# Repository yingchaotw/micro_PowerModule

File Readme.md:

# µPower Module

1. Purpose：

 - DC/DC Programmable small-wattage power supply
 - This project is [Open Source Hardware](https://www.oshwa.org/definition/chinese/)

2. Scope：
 - RFQ
     1. [x] Over voltage protection circuit
     2. [x] Support [MikroBus](https://www.mikroe.com/mikrobus) Foot Position
     3. [x] Positive and negative load voltage signals can be controlled by the H-bridge
     4. [x] Display voltage/current/wattage [Nokia 5110 LCD](https://github.com/EleonoreMizo/pedalevite/blob/master/doc/datasheets/Philips%20PCD8544%20-%20IC%2C%2048x84%20pixels%20matrix%20LCD%20controller%20(Nokia%205110).pdf), [TI-Nokia 5110 LCD](https://www.ti.com/lit/ml/swrp182/swrp182.pdf), [Nokia5110 LCD ](https://components101.com/displays/nokia-5110-lcd)
     5. [ ] MCU auto-regulator function
     6. [ ] Real time display of voltage and current
     7. [ ] Use a led to display local or remote mode
        1. [x] Standard Commands for Programmable Instruments

# HW Block Diagram

<BR/>
plug-in module. ex. Temperature sensor, etc.. <br/>

[Schematic Readme](./Circuit_microPowerModule/Readme.md)

# SW FlowChart
```mermaid
flowchart TD
subgraph "System Initialization"
  a("Check Communication<BR>(UART/I2C/SPI/..)") --> b(Check ADC) --> c(Read Sensor) --> d[buzzer <br> Make a sound]
end

subgraph "main"
    A(Start) --> B[System<br>Initialization]
    B --> C[Select Mode]
    C -->D["Remote <PC>"]
    C -->E["Local <encoder>"]
end

```

# Candidate Components

The required hardware units are divided into the following 6 items.
1. Power
2. Microcontroller
3. Interface
4. Sensor (Current/temperature)
5. Connector
6. Debug port

# PIN Assessment

[Raspberry Pi RP2040 GPIO Function](https://datasheets.raspberrypi.com/rp2040/rp2040-datasheet.pdf#_gpio_functions)

```
GPIO00 UART0 (Tx) --> RS485 (In)
GPIO01 UART0 (Rx) <-- RS485 (Out)
GPIO02 I2C1 (SDA) <-> (*Option) MikroBus SDA
GPIO03 I2C1 (SCL) --> (*Option) MikroBus SCL
GPIO04 I2C0 (SDA) <-> Power Management
GPIO05 I2C0 (SCL) --> Power Management
GPIO06 DS (MOSI)  --> Display Serial Input
GPIO07 DS (CLK)   --> Display Clock Input
GPIO08 UART1 (Tx) --> (*Option) MikroBus Tx
GPIO09 UART1 (Rx) <-- (*Option) MikroBus Rx
GPIO10 SPI1 (SCK) --> (*Option) MikroBus SCK
GPIO11 SPI1 (Tx)  --> (*Option) MikroBus SDI
GPIO12 SPI1 (Rx)  <-- (*Option) MikroBus SDO
GPIO13 SPI1 (nCS) --> (*Option) MikroBus CSS
GPIO14 DS (CE)    --> Display Chip Enable
GPIO15 DS (DC)    --> Display Data Command
GPIO16 PWM0_A     --> Buzzer
GPIO17 MkBus_RST  --> (*Option) MikroBus Reset
GPIO18 PWM1_A     --> (*Option) MikroBus PWM
GPIO19 PIO1_IRQ1  --> (*Option) MikroBus INT
GPIO20 PWM2_A     --> Encoder A phase
GPIO21 PWM2_B     --> Encoder B phase
GPIO22 RS_485 W/R --> RS485 (W/R)
GPIO23 DS_RST     --> Display Reset
GPIO24 ENC_SW     <-- Encoder Push Switch
GPIO25 PWM4 B     --> WS2512 LED Control
GPIO26 Monitor    <-- Input Power Monitor
GPIO27 ADC1       <-- (*Option) MikroBus ADC
GPIO28 Output_CTRL<-- Buck / Boost Switch
GPIO29 *Polarity  --> H-Bridge Control Load (Forward/Reverse)
```

# Potocol

[About Spec](./Document/Specification/Spec_link.md)
[Standard Commands for Programmable Instruments](https://www.ivifoundation.org/docs/scpi-99.pdf)

# Licenses & Disclaimer

 <br/> This work is licensed under a <a rel="license" href="https://www.gnu.org/licenses/quick-guide-gplv3.en.html"> GNU General Public License v3</a>.

If you have other ideas or suggestions, please feel free to submit an issue.
Welcome fork this repositories to provide contributions, or [buy me a coffee](https://ko-fi.com/yingchao_tw). thanks :)

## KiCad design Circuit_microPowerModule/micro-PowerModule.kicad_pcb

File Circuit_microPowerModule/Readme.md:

# Schematic

# ERC Report

```
ERC report (Thu 15 Jun 2023 20:53:31 CST, Encoding UTF8)

***** Sheet /

***** Sheet /main_contorl/

***** Sheet /Input_power/

***** Sheet /OutputPower/

***** Sheet /peripheral/

** ERC messages: 0  Errors 0  Warnings 0
```
[ERC File](./ERC.rpt)

# Incldue Library
[MikroBus](https://github.com/tclarke/kicad-mikroBUS)

# License & Disclaimer

 <br/> This work is licensed under a <a rel="license" href="https://www.gnu.org/licenses/quick-guide-gplv3.en.html"> GNU General Public License v3</a>.

If you have other ideas or suggestions, please feel free to submit an issue.
Welcome fork this repositories to provide contributions, or [buy me a coffee](https://ko-fi.com/yingchao_tw). thanks :)

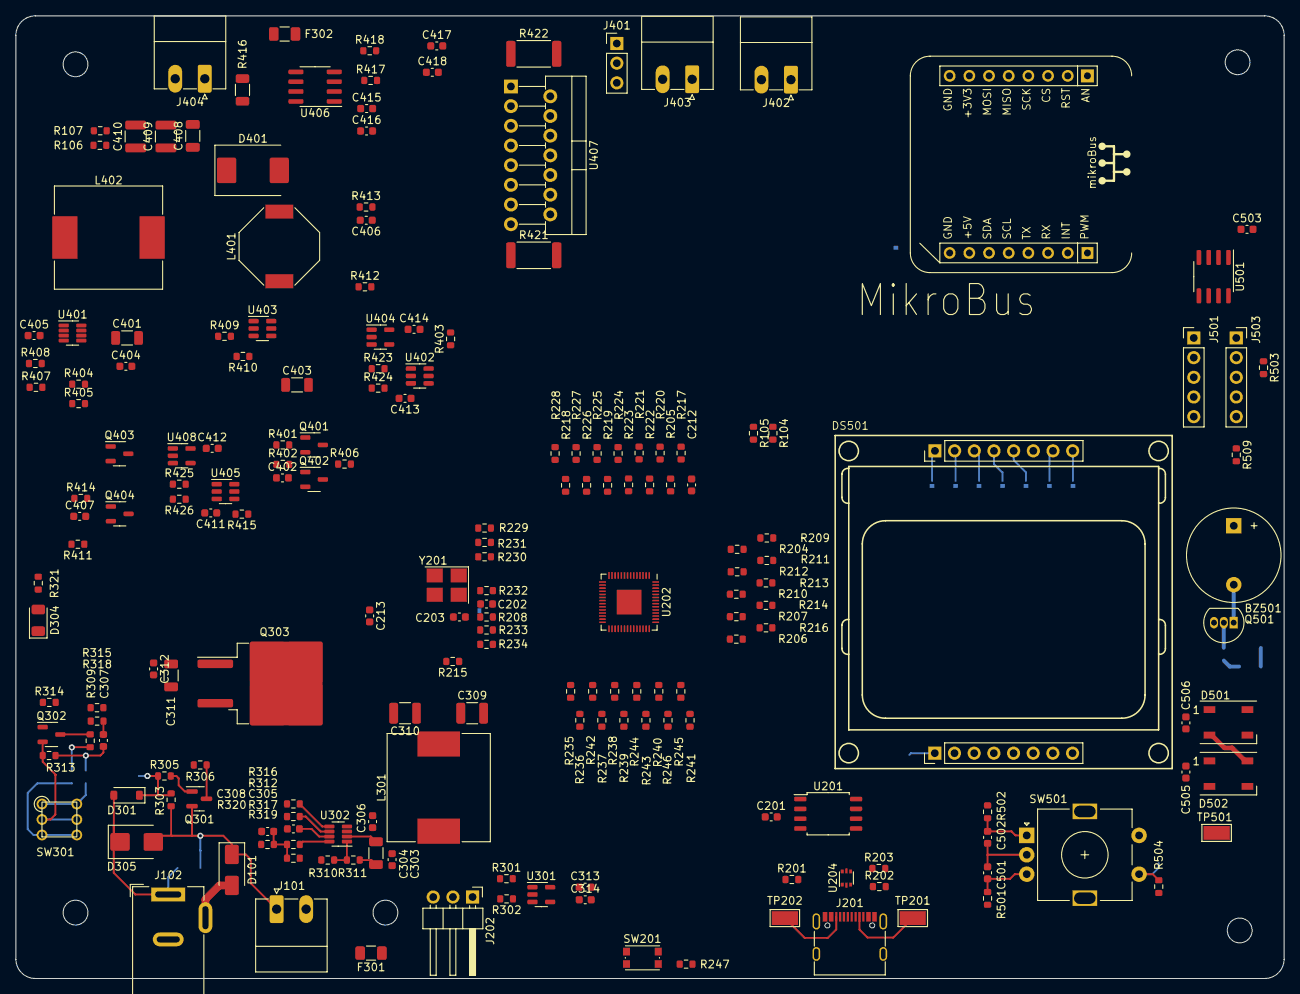
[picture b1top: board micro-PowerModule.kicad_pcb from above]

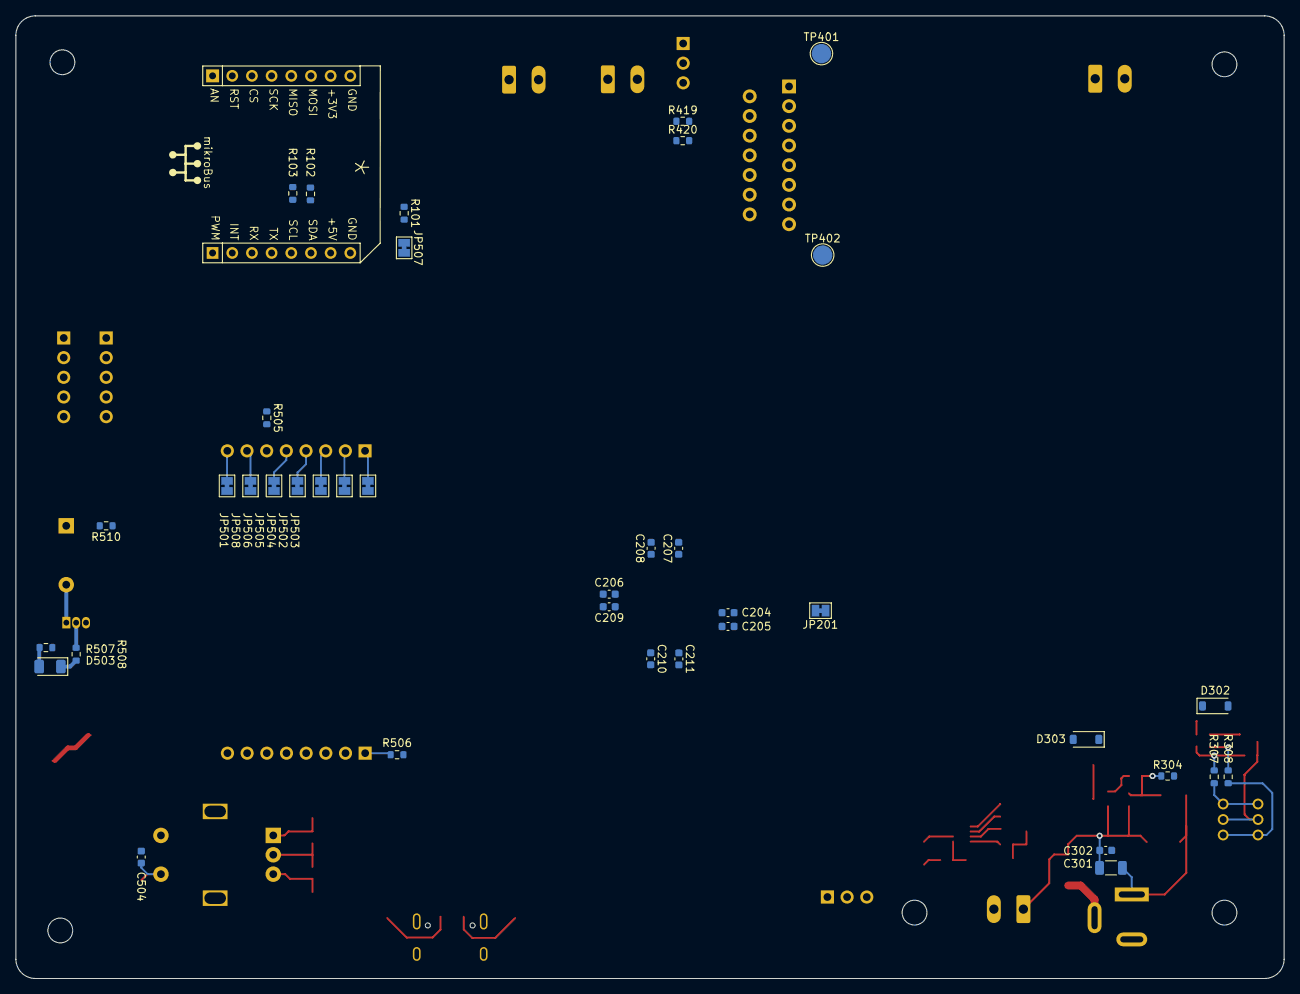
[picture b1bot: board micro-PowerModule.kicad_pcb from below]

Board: 2 copper layers, 163.7 x 124.2 mm, 235 parts (38 on the bottom side), 177 nets.

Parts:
BZ501: Buzzer; Buzzer_12x9.5RM7.6
C201, C204, C205, C206, C207, C208, C209, C210, C211, C212, C303, C305, C306, C313, C314, C404, C405, C411, C412, C413, C414, C415, C416, C417, C418, C501, C502, C503, C505, C506: 100nF/50V; C_0603_1608Metric
C202, C203: 15pF/50V; C_0603_1608Metric
C213, C402, C407: 10pF/50V; C_0603_1608Metric
C301, C311: 47u/50V; C_1206_3216Metric
C302, C312: 100n/50V; C_0603_1608Metric
C304, C401, C403, C408: 22uF/50V; C_1206_3216Metric
C307: 10n/50V; C_0603_1608Metric
C308, C406: 33pF/50V; C_0603_1608Metric
C309, C310, C409, C410: 22uF/50V; C_1210_3225Metric
C504: 10nF/50V; C_0603_1608Metric
D101: SS54; D_SMA
D301: Zener_24V/500mW; D_SOD-123
D302: DNP; D_SOD-123
D303: Zener_20V/500mW; D_SOD-123
D304: LED_Green; LED_1206_3216Metric
D305: TPSMB36CA; D_SMB
D401: SS34; D_SMC
D501, D502: WS2812B; LED_WS2812B_PLCC4_5.0x5.0mm_P3.2mm
D503: LED_Blue; LED_1206_3216Metric
DS501: NOKIA 5110; Nokia_5110_module
F301, F302: 60V/100mA; Fuse_1206_3216Metric
J101, J402, J403, J404: Screw_Terminal_01x02; PhoenixContact_MC_1,5_2-G-3.81_1x02_P3.81mm_Horizontal
J102: Jack-DC; BarrelJack_Wuerth_6941xx301002
J201: USB_C_Receptacle_USB2.0; USB_C_Receptacle_G-Switch_GT-USB-7010ASV
J202: Debug; PinHeader_1x03_P2.54mm_Horizontal
J401: Conn_01x03; PinHeader_1x03_P2.54mm_Vertical
J501: HDR-2.54 Male 1x5; PinHeader_1x05_P2.54mm_Vertical
J502: MikroBus; MIKROBUS_CONN
J503: HDR-2.54 Female 1x5; PinSocket_1x05_P2.54mm_Vertical
JP201, JP501, JP502, JP503, JP504, JP505, JP506, JP507, JP508: SolderJumper_2_Bridged; SolderJumper-2_P1.3mm_Bridged_Pad1.0x1.5mm
L301, L402: 4.7uH; L_Sunlord_MWSA1204S-4R7
L401: 33uH; L_Bourns-SRU1028_10.0x10.0mm
Q301: MMBT3906; SOT-23
Q302, Q402, Q404: RK7002BM; SOT-23-3
Q303: IRF5305S; TO-263-2
Q401, Q403: RU1C002ZP; SOT-23-3
Q501: S8550; TO-92_Inline
R101, R201, R216, R309, R318, R401, R411, R417, R418, R423, R425, R506, R509, R510: 0R/5%; R_0603_1608Metric
R102, R103, R106, R107, R204, R205, R303, R304, R305, R306, R307, R501, R502, R504: 10K/5%; R_0603_1608Metric
R104, R105: 22R/5%; R_0603_1608Metric
R202, R203: 5.1K/5%; R_0603_1608Metric
R206, R207: 27R/5%; R_0603_1608Metric
R208, R314, R321, R403, R415, R419, R420, R424, R426, R507, R508: 1K/5%; R_0603_1608Metric
R209, R210, R211, R212, R213, R214, R217, R218, R219, R220, R221, R222, R223, R224, R225, R226, R227, R228, R229, R230, R231, R232, R233, R234, R235, R236, R237, R238, R239, R240, R241, R242, R243, R244, R245, R246, R316, R407: 10R/5%; R_0603_1608Metric
R215, R247: 1K/DNP; R_0603_1608Metric
R301, R402, R414: 22K/5%; R_0603_1608Metric
R302: 3.3K/5%; R_0603_1608Metric
R308: 100R/5%; R_0603_1608Metric
R310, R313, R315, R404, R408: 100K/5%; R_0603_1608Metric
R311: 7.5K/5%; R_0603_1608Metric
R312: 499K/5%; R_0603_1608Metric
R317: 33K/5%; R_0603_1608Metric
R319: 12.7K/5%; R_0603_1608Metric
R320: 40.2K/5%; R_0603_1608Metric
R405: 9K1/5%; R_0603_1608Metric
R406: 47R/5%; R_0603_1608Metric
R409, R410: 2.2K/5%; R_0603_1608Metric
R412: 62K/5%; R_0603_1608Metric
R413: 20.5K/5%; R_0603_1608Metric
R416: 0.1R/1%; R_1206_3216Metric
R421, R422: 0.5R/5%; R_2512_6332Metric
R503: 120R/5%; R_0603_1608Metric
R505: DNP; R_0603_1608Metric
REF1, REF1#2, REF1#3, REF1#4, REF1#5: MountingHole_3.2mm_M3_ISO7380
SW201: KMR2; SW_Push_1P1T_NO_CK_KMR2
SW301: SW_DPDT_x2; SW_DIP_5176_SPDT
SW501: RotaryEncoder_Switch; RotaryEncoder_Alps_EC11E-Switch_Vertical_H20mm
TP201, TP202, TP501: TestPoint_Small; TestPoint_Keystone_5015_Micro-Minature
TP401, TP402: TestPoint; TestPoint_Pad_D2.5mm
U201: W25Q128JVS; SOIC-8_5.23x5.23mm_P1.27mm
U202: RP2040; QFN-56-1EP_7x7mm_P0.4mm_EP3.2x3.2mm
U204: USBLC6-2P6; SOT-666
U301, U404, U408: OPA376xxDBV; SOT-23-5
U302, U401: MP2315S; TSOT-23-8
U402, U405: MCP4725xxx-xCH; SOT-23-6
U403: MT3608; SOT-23-6
U406: INA219BxD; SOIC-8_3.9x4.9mm_P1.27mm
U407: L298N; TO-220-15_P2.54x2.54mm_StaggerOdd_Lead4.58mm_Vertical
U501: MAX485E; SOIC-8_3.9x4.9mm_P1.27mm
Y201: 12MHz; Crystal_SMD_SeikoEpson_FA238V-4Pin_3.2x2.5mm_HandSoldering

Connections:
+1V2: C204.1, C205.1, C206.1, R216.1, U202.23 (DVDD), U202.50 (DVDD)
+3V3: C201.1, C207.1, C208.1, C209.1, C210.1, C211.1, C212.1, C308.2, C309.1, C310.1, C313.1, C314.1, C411.1, C412.1, C413.1, C414.1, C415.1, C416.1, C503.1, C505.1, C506.1, D501.1 (VDD), D502.1 (VDD), J502.7, JP508.2 (B), L301.2, Q401.1 (D), Q403.1 (D), R102.1, R103.1, R106.1, R107.1, R204.2, R205.2, R247.1, R320.1, R402.2, R414.2, R415.2, R419.1, R501.1, R502.1, R504.1, R506.1, R507.1, R510.1, U201.8 (VCC), U202.1 (IOVDD), U202.10 (IOVDD), U202.22 (IOVDD), U202.33 (IOVDD), U202.42 (IOVDD), U202.43 (ADC_AVDD), U202.44 (VREG_IN), U202.48 (USB_VDD), U202.49 (IOVDD), U301.5 (V+), U402.3 (VDD), U404.5 (V+), U405.3 (VDD), U406.5 (VS), U408.5 (V+), U501.8 (VCC)
+5V: C417.1, C418.1, J502.10, R509.2, U407.4 (Vs)
+VDC: C303.1, C304.1, C311.1, C312.1, C401.1, C403.1, L401.1, Q303.1 (D), R312.2, R321.1, U302.2 (IN), U401.2 (IN), U403.5 (IN)
/BUCK/~BOOST: R104.2, R245.2
/Buzzer_PWM: D503.1 (K), R233.2, R508.1
/Forward/~Reverse: R105.2, R246.2
/Mk_ADC: J502.1, R244.2
/Mk_CS: J502.3, R230.2
/Mk_INT: J502.15, R236.2
/Mk_PWM: J502.16, R235.2
/Mk_RST: J502.2, R234.2
/Mk_Rx: J502.14, R226.2
/Mk_SCL: J502.12, R103.2, R220.2
/Mk_SDA: J502.11, R102.2, R219.2
/Mk_SDI: J502.6, R228.2
/Mk_SDK: J502.4, R227.2
/Mk_SDO: J502.5, R229.2
/Mk_Tx: J502.13, R225.2
/OutputPower/Boost_FB: R410.2, U408.1, U408.4 (-)
/OutputPower/BuckBoostOutput: C408.1, C409.1, C410.1, D401.1 (K), L402.2, R409.1, R416.1, U406.8 (IN+)
/OutputPower/Buck_EN/Boost_~EN: R104.1, R401.1
/OutputPower/Buck_FB: R412.2, U404.1, U404.4 (-)
/OutputPower/EN_MP2315S: C402.1, Q401.2 (G), Q402.2 (G), R401.2, R402.1, U401.6 (EN)
/OutputPower/EN_MT3608: R406.2, U403.4 (EN)
/OutputPower/H_Bridge_Out1: J402.1, U407.2 (OUT1)
/OutputPower/H_Bridge_Out2: J402.2, U407.3 (OUT2)
/OutputPower/H_Bridge_Out3: J403.1, U407.13 (OUT3)
/OutputPower/H_Bridge_Out4: J403.2, U407.14 (OUT4)
/OutputPower/Load_Forward: C407.1, Q403.2 (G), Q404.2 (G), R411.2, R414.1, U407.5 (IN1), U407.10 (IN3)
/OutputPower/Load_Reverse: Q403.3 (S), Q404.1 (D), U407.7 (IN2), U407.12 (IN4)
/OutputPower/Load_direction: R105.1, R411.1
/OutputPower/PWR_OUT: C406.2, J404.1, R413.1, R416.2, U406.7 (IN-), U407.9 (Vss)
/PM_SCL: R106.2, R221.2, U402.5 (SCL), U405.5 (SCL), U406.4 (SCL)
/PM_SDA: R107.2, R222.2, U402.4 (SDA), U405.4 (SDA), U406.3 (SDA)
/PWR_IN: C301.1, C302.1, C307.1, D101.1 (K), D303.1 (K), D305.2 (A2), J101.1, Q301.2 (E), Q303.3 (S), R301.1, R303.1, R307.1, R313.1, R315.1
/PWR_Monitor: R243.2, U301.1, U301.4 (-)
/RP_DS_CHIPENABLE: JP502.1 (A), R231.2
/RP_DS_CLK: JP506.1 (A), R224.2
/RP_DS_DATACMD: JP504.1 (A), R232.2
/RP_DS_MOSI: JP505.1 (A), R223.2
/RP_DS_RESET: JP503.1 (A), R240.2
/RP_ENC_A: C502.1, R237.2, R502.2, SW501.A
/RP_ENC_B: C501.1, R238.2, R501.2, SW501.B
/RP_ENC_SW: C504.1, R241.2, R504.2, SW501.S1
/UARTrx_RS485in: R217.2, U501.4 (DI)
/UARTtx_RS485out: R218.2, U501.1 (RO)
/main_contorl/LET_CTRL: D501.4 (DIN), R242.2
/main_contorl/QSPI_NSS: R204.1, R209.2, U201.1 (~CS)
/main_contorl/QSPI_SCLK: R214.2, U201.6 (CLK)
/main_contorl/QSPI_SD0: R210.2, U201.5 (DI(IO0))
/main_contorl/QSPI_SD1: R211.2, U201.2 (DO(IO1))
/main_contorl/QSPI_SD2: R212.2, U201.3 (IO2)
/main_contorl/QSPI_SD3: R213.2, U201.7 (IO3)
/main_contorl/RS485_W/~R: R239.2, U501.2 (~RE), U501.3 (DE)
/main_contorl/SWCLK: J202.1, U202.24 (SWCLK)
/main_contorl/SWDIO: J202.3, U202.25 (SWD)
/main_contorl/USB+: R206.2, U204.4 (I/O2)
/main_contorl/USB-: R207.2, U204.6 (I/O1)
/main_contorl/USB_N: J201.A7 (D-), J201.B7 (D-), U204.1 (I/O1)
/main_contorl/USB_P: J201.A6 (D+), J201.B6 (D+), U204.3 (I/O2)
/main_contorl/~RESET: C213.1, R205.1, R247.2, SW201.2, U202.26 (RUN)
/main_contorl/~USB_N: R207.1, U202.46 (USB_DM)
/main_contorl/~USB_P: R206.1, U202.47 (USB_DP)
/peripheral/485A: J501.3, J503.3, R503.2, U501.6 (A)
/peripheral/485B: J501.2, J503.2, R503.1, U501.7 (B)
/peripheral/DS_Backlight: DS501.7b (BL), DS501.8a (BL), JP508.1 (A)
/peripheral/DS_ChipEnable: DS501.2b (CE), DS501.3a (SEC), JP502.2 (B)
/peripheral/DS_Clock: DS501.5b (CLK), DS501.7a (SCLK), JP506.2 (B)
/peripheral/DS_Data/Command: DS501.3b (DC), DS501.5a (D/C), JP504.2 (B)
/peripheral/DS_Serial_Data: DS501.4b (DIN), DS501.6a (DN/MOSI), JP505.2 (B)
/peripheral/DS_~Reset: DS501.1b (RST), DS501.4a (RST), JP503.2 (B)
/peripheral/M_GND: J502.8, J502.9, JP507.2 (B)
/peripheral/Mikro_GND: JP507.1 (A), R101.2
GNDPWR: C301.2, C302.2, C303.2, C304.2, C305.2, C309.2, C310.2, C311.2, C312.2, C401.2, C403.2, C404.2, C408.2, C409.2, C410.2, D301.2 (A), D304.1 (K), D305.1 (A1), F301.2, F302.1, J101.2, J102.1, J102.2, J404.2, R304.2, R306.2, R308.2, R309.2, R311.1, R319.2, R405.1, R421.2, R422.2, U302.4 (GND), U401.4 (GND), U403.2 (GND), U407.8 (GND)
GNDREF: C201.2, C204.2, C205.2, C206.2, C207.2, C208.2, C209.2, C210.2, C211.2, C212.2, C213.2, C313.2, C314.2, C402.2, C407.2, C411.2, C412.2, C413.2, C414.2, C415.2, C416.2, C417.2, C418.2, C501.2, C502.2, C503.2, C504.2, C505.2, C506.2, D501.3 (VSS), D502.3 (VSS), DS501.2a (GND), DS501.8b (GND), F301.1, F302.2, J201.A1 (GND), J201.A12 (GND), J201.B1 (GND), J201.B12 (GND), J202.2, JP201.1 (A), JP501.1 (A), Q402.3 (S), Q404.3 (S), Q501.3 (C), R101.1, R201.2, R202.2, R203.1, R302.2, R403.2, R417.2, R418.2, R420.2, R424.1, R426.1, SW201.1, SW501.C, SW501.S2, U201.4 (GND), U202.57 (GND), U204.2 (GND), U301.2 (V-), U402.2 (VSS), U404.2 (V-), U405.2 (VSS), U406.6 (GND), U408.2 (V-), U501.5 (GND), Y201.2, Y201.4
unnamed: BZ501.2 (+), Q501.1 (E)
unnamed: BZ501.1 (-), R510.2
unnamed: C202.1, Y201.1
unnamed: C203.1, Y201.3
unnamed: C203.2, R208.2
unnamed: C306.1, R316.2
unnamed: C308.1, R317.1, R319.1, R320.2
unnamed: C405.1, R407.2
unnamed: C406.1, R408.1, R412.1, R413.2
unnamed: D101.2 (A), J102.3
unnamed: D301.1 (K), R303.2, R304.1, R305.1
unnamed: D302.2 (A), R314.2, R315.2, R318.1
unnamed: C307.2, D302.1 (K), D303.2 (A), Q303.2 (G), R318.2
unnamed: D304.2 (A), R321.2
unnamed: D401.2 (A), L401.2, U403.1 (SW)
unnamed: D501.2 (DOUT), D502.4 (DIN)
unnamed: D502.2 (DOUT), TP501.1
unnamed: D503.2 (A), R507.2
unnamed: DS501.1a (VCC), DS501.6b (VCC), R505.2, R506.2
unnamed: J201.A5 (CC1), R202.1
unnamed: J201.B5 (CC2), R203.2
unnamed: J201.A8 (SBU1), TP201.1
unnamed: J201.B8 (SBU2), TP202.1
unnamed: J201.S1 (SHIELD), R201.1
unnamed: J401.1, R419.2
unnamed: J401.2, U407.6 (EnA), U407.11 (EnB)
unnamed: J401.3, R420.1
unnamed: J501.1, J503.1, JP501.2 (B)
unnamed: JP201.2 (B), U202.19 (TESTEN)
unnamed: Q301.1 (B), R305.2
unnamed: Q301.3 (C), R306.1
unnamed: Q302.1 (D), R314.1
unnamed: Q302.2 (G), R313.2, SW301.2 (B), SW301.5 (B)
unnamed: Q302.3 (S), R309.1
unnamed: Q401.3 (S), Q402.1 (D), R406.1
unnamed: Q501.2 (B), R508.2
unnamed: R307.2, SW301.1 (A), SW301.4 (A)
unnamed: R308.1, SW301.3 (C), SW301.6 (C)
unnamed: R217.1, U202.2 (GPIO0)
unnamed: R218.1, U202.3 (GPIO1)
unnamed: R219.1, U202.4 (GPIO2)
unnamed: R220.1, U202.5 (GPIO3)
unnamed: R221.1, U202.6 (GPIO4)
unnamed: R222.1, U202.7 (GPIO5)
unnamed: R223.1, U202.8 (GPIO6)
unnamed: R224.1, U202.9 (GPIO7)
unnamed: R225.1, U202.11 (GPIO8)
unnamed: R226.1, U202.12 (GPIO9)
unnamed: R227.1, U202.13 (GPIO10)
unnamed: R228.1, U202.14 (GPIO11)
unnamed: R229.1, U202.15 (GPIO12)
unnamed: R230.1, U202.16 (GPIO13)
unnamed: R231.1, U202.17 (GPIO14)
unnamed: R232.1, U202.18 (GPIO15)
unnamed: R233.1, U202.27 (GPIO16)
unnamed: R234.1, U202.28 (GPIO17)
unnamed: R235.1, U202.29 (GPIO18)
unnamed: R236.1, U202.30 (GPIO19)
unnamed: R237.1, U202.31 (GPIO20)
unnamed: R238.1, U202.32 (GPIO21)
unnamed: R239.1, U202.34 (GPIO22)
unnamed: R240.1, U202.35 (GPIO23)
unnamed: R241.1, U202.36 (GPIO24)
unnamed: R242.1, U202.37 (GPIO25)
unnamed: R243.1, U202.38 (GPIO26_ADC0)
unnamed: R244.1, U202.39 (GPIO27_ADC1)
unnamed: R245.1, U202.40 (GPIO28_ADC2)
unnamed: R246.1, U202.41 (GPIO29_ADC3)
unnamed: R214.1, U202.52 (QSPI_SCLK)
unnamed: R210.1, U202.53 (QSPI_SD0)
unnamed: R211.1, U202.55 (QSPI_SD1)
unnamed: R212.1, U202.54 (QSPI_SD2)
unnamed: R213.1, U202.51 (QSPI_SD3)
unnamed: R209.1, U202.56 (QSPI_SS)
unnamed: R216.2, U202.45 (VREG_VOUT)
unnamed: C202.2, R215.1, U202.20 (XIN)
unnamed: R208.1, R215.2, U202.21 (XOUT)
unnamed: R301.2, R302.1, U301.3 (+)
unnamed: R310.1, R311.2, U302.1 (AAM)
unnamed: R316.1, U302.5 (BST)
unnamed: R312.1, U302.6 (EN)
unnamed: R317.2, U302.8 (FB)
unnamed: C306.2, L301.1, U302.3 (SW)
unnamed: C305.1, R310.2, U302.7 (VCC)
unnamed: R404.1, R405.2, U401.1 (AAM)
unnamed: R407.1, U401.5 (BST)
unnamed: R408.2, U401.8 (FB)
unnamed: C405.2, L402.1, U401.3 (SW)
unnamed: C404.1, R404.2, U401.7 (VCC)
unnamed: R403.1, U402.6 (A0)
unnamed: R423.2, U402.1 (VOUT)
unnamed: R409.2, R410.1, U403.3 (FB)
unnamed: R423.1, R424.2, U404.3 (+)
unnamed: R415.1, U405.6 (A0)
unnamed: R425.2, U405.1 (VOUT)
unnamed: R418.1, U406.2 (A0)
unnamed: R417.1, U406.1 (A1)
unnamed: R422.1, TP401.1, U407.1 (SENSE_A)
unnamed: R421.1, TP402.1, U407.15 (SENSE_B)
unnamed: R425.1, R426.2, U408.3 (+)
VBUS: J201.A4 (VBUS), J201.A9 (VBUS), J201.B4 (VBUS), J201.B9 (VBUS), J501.5, J503.5, R505.1, R509.1, U204.5 (VBUS)

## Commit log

2023-05-17 added/modify readme file text
2023-05-18 create HW block diagram
    added shopee purchase list
2023-05-19 update HW block diagram
    added kicad schematic, sw flowchart
2023-05-20 decision MCU-RP2040
    added RP2040 to circuit
2023-05-22 added MP2315S lib, updated circuit
    updated block diagram by-sa
2023-05-23 new RFQ, update circuit
2023-05-24 added input power OVP circuit
    update buck-boost circuit
2023-05-25 added boost circuit
    create peripheral schematic
2023-05-26 added mikrobus header
    added filter capacitance, I2C pull-up resistor
2023-05-27 added Nokia 5110 LCD symbol
    linked some component pin
2023-05-28 added schematic svg file
    added encoder wire, mikrobus connect
2023-05-30 define mcu pinout to mikrobus
    update hw block diagram file type
2023-05-31 Completed microcontroller unit pin planning
    update schematic
2023-06-05 change licenses
    updated some footprint, create nokia 5110 lcd module pcb symbol, updated reademe
2023-06-06 update components footprint
    check boost VR component, added Nokia 5110 LCD 3D module
2023-06-10 update schematic
    added pin assessment to readme
2023-06-11 added protocol document
    update pin assessment
2023-06-13 added H-Bridge
    Control load forward or reverse (current direction)
2023-06-14 modify ERC error, protect components
2023-06-15 modify ERC warning
    modify OPA, TVS-Diode, Cap
2023-06-16 start pcb layout
2023-06-17 update pcb layout component
    target to smaller pcb size
2023-06-19 set board edge cut
2023-06-21 Finishing MCU Peripheral Passive Components
2023-06-22 update system power circuit layout
2023-06-27 update output inductor footprint
2023-06-29 modify DAC to Voltage follwers
2023-07-05 update pcb component layout
2023-07-13 update pcb trace layout
2023-07-15 update U302 PCB Layout

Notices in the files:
Readme.md:
license - GPLv3
